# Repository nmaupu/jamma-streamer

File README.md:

# jamma-streamer

Jamma PCB video recorder and more (hardware)

# Eagle library and parts used

* `nma-eagle` library: https://github.com/nmaupu/electronics/blob/master/eagle-libs/nma-eagle.lbr
* SparkFun libraries (https://github.com/sparkfun/SparkFun-Eagle-Libraries):
  - SparkFun-Connectors
  - SparkFun-IC-Comms
  - SparkFun-PowerSymbols
  - SparkFun-Retired
* Default eagle libraries:
  - linear
  - pinhead
  - jumper

# BOM (Bill Of Materials) generation

To generate the BOM, use process described in [electronics](https://github.com/nmaupu/electronics) repository !

# RTC

## Interrupts for milliseconds counting

* We will be using the chip `DS3231`. Pin `INT/SWQ` is the one.
* Datasheet https://datasheets.maximintegrated.com/en/ds/DS3231.pdf page 13 indicates how to configure the register to enable a 1KHz signal on this pin.
* The configuration of the register should be: `0b10001000`.
* Configuration is done using I2C protocol.
* `PC3` for `pin change interrupt` on the ATmega side.

Example on how to use `PCINT` is available here: https://gist.github.com/Wollw/2598827

Example on how to configure chip registers via I2C: https://github.com/FabioCuomo/FabioCuomo-DS3231/blob/master/RTClibExtended.cpp

# Buttons detection

Buttons detection are done using shift registers (8 bits parallel in / serial out such as the 75HC165).
The code used is strongly inspired from the following tutorial:
https://playground.arduino.cc/Code/ShiftRegSN74HC165N

# uSDCARD writing

Source:
https://learn.adafruit.com/adafruit-micro-sd-breakout-board-card-tutorial?view=all

Beware: Arduino pins number and macros you can use in your code are sometimes not equivalent to what you expect when using third party libraries like the one used for SD card... One example is the pin `PB2` (Arduino's pin number 10) used for `CS`. If you use the library's macro `PB2`, it sets the pin to number `2` instead of `10`... This leads to long painful debugging session...

Here is an image with all pin numbers as a reference:

# How to program the ATMEGA328PB

## Fuses

Fuses can be calculated using: https://www.engbedded.com/fusecalc/

More info here: http://www.martyncurrey.com/arduino-atmega-328p-fuse-settings/

## Using arduino bootloader (for debugging and fast upload via IDE)

We are going to use [Minicore](https://github.com/MCUdude/MiniCore) as it supports ATmega328PB used on this project.

---

Use the following procedure:

- First install minicore boards following the [procedure](https://github.com/MCUdude/MiniCore#boards-manager-installation).

Use *arduino as ISP* method to upload the bootloader:
  - configure your IDE to use the source Arduino which will act as a programmer (ISP programmer)
  - upload Arduino ISP sketch to the arduino board to make it act as an *ISP programmer* (available as example sketch from the Arduino IDE)
  - plug all *Jamma Streamer's ICSP* to *Arduino ICSP* except *RST* both sides
  - *RST Jamma Streamer* (from ICSP) to *pin 10* of the Arduino (this will act as the reset pin)
  - plug a 10uF capacitor between Arduino RESET (capacitor +) and GND (capacitor -)

Now configure the board as per the following:

Your arduino is ready for ISP. Now you can configure to burn the bootloader:
  - `Tools > Port`: select the arduino device
  - `Tools > Burn Bootloader`

This should work as expected. From now on, you will be able to upload sketches via *NMA Jamma Streamer* USB port directly!

Fuses consideration:
  - *Minicore* is forked from *Optiboot* (official Arduino UNO bootloader) and is `512 bytes` long.
  - We are using an external crystal oscillator (and not the internal one).
  - `EEPROM` save is enabled (this avoid erasing it at each upload reducing its lifetime).
  - `BOOTSZ1` and `BOOTSZ2` are both disabled because 512 bytes can fit into the minimal 256 words (1 word = 2 bytes).
  - `BOOTRST` is set to indicate we are using a bootloader.
  - `BODLEVEL1` (2.7V) is enabled because why not.

This give the following fuses:
  - low fuse: `0xff`
  - high fuse: `0xd6`
  - extended fuse: `0xf5` (Normally, it would be `0xfd` but after burning, there is a warning so `f5` is a good value)

## Without using arduino bootloader for runtime

We are using Jamma Streamer board ICSP header for this.
No need for a Arduino bootloader, we will be uploading sketch directly via ICSP header !

As I am using Atmega328PB (instead of P), Arduino IDE is not recognizing at first, we need to install this first to have the board available in Arduino’s IDE later on:
https://github.com/nmaupu/ATmega328PB-Testing

---

Plug cables as follow (using Arduino Duemilanove or Mega):

- All ICSP to Arduino ICSP except RST both sides
- RST Jamma Streamer (from icsp) to pin 10 of the arduino
- Plug Arduino via USB to computer and upload ArduinoISP sketch onto it.
- plug a 10uF capacitor between Arduino RESET (capacitor +) and GND (capacitor -)
- select tools > boards > atmega328PB Crystal Clock
- `sketch > Upload using programmer`

This will program the NMA Jamma Streamer ATmega328PB !

## Burn / read fuses (use the crystal oscillator instead of internal one)

Use an external Arduino board to act as an ISP programmer like before:

- All ICSP to Arduino ICSP except RST both sides
- RST Jamma Streamer (from icsp) to pin 10 of the arduino
- Plug Arduino via USB to computer and upload ArduinoISP sketch onto it.
- plug a 10uF capacitor between Arduino RESET (capacitor +) and GND (capacitor -)

To read the fuses, simply execute:
```
avrdude -C /Users/nicolas_maupu/Library/Arduino15/packages/MiniCore/hardware/avr/2.0.5/avrdude.conf \
  -p atmega328pb -c stk500v1 -P /dev/cu.usbmodem141101 -b19200 \
  -U hfuse:r:-:h -U efuse:r:-:h -U lfuse:r:-:h
```

To burn fuses:
```
avrdude -C /Users/nicolas_maupu/Library/Arduino15/packages/MiniCore/hardware/avr/2.0.5/avrdude.conf \
  -v -p atmega328pb -c stk500v1 -P /dev/cu.usbmodem141101 -b19200 \
  -e -Ulock:w:0x3f:m -Uefuse:w:0xF5:m -Uhfuse:w:0xd6:m -Ulfuse:w:0xff:m 
```

To burn the Minicore bootloader:
```
avrdude -C /Users/nicolas_maupu/Library/Arduino15/packages/MiniCore/hardware/avr/2.0.5/avrdude.conf \
  -v -p atmega328pb -c stk500v1 -P /dev/cu.usbmodem141101 -b19200 \
  -Uflash:w:$HOME/Library/Arduino15/packages/MiniCore/hardware/avr/2.0.5/bootloaders/optiboot_flash/bootloaders/atmega328pb/16000000L/optiboot_flash_atmega328pb_UART0_115200_16000000L_B5.hex:i \
  -Ulock:w:0x0f:m 
```

# Thanks

- https://github.com/Shinichi-Ohki/JAMMA_connector_for_eagle
- https://github.com/watterott/wattuino

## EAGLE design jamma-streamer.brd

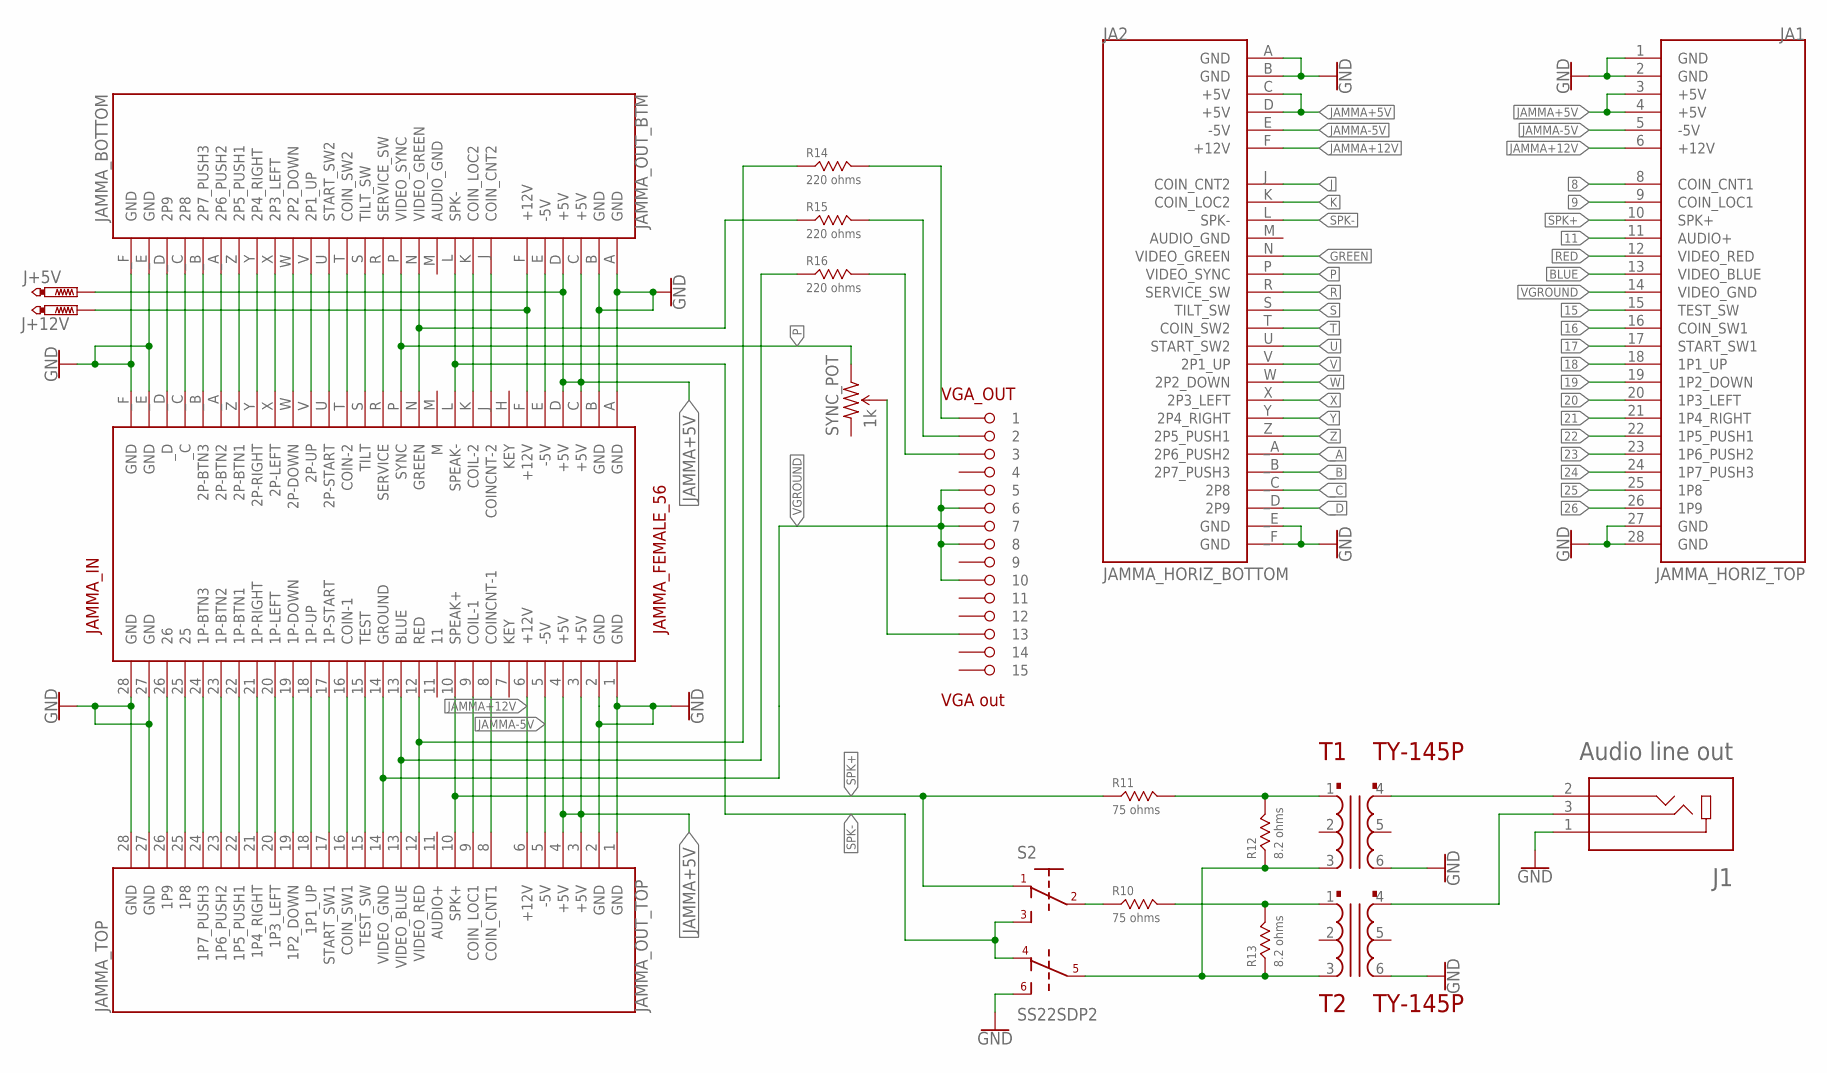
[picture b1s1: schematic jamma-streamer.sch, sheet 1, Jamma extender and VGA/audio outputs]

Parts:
J1: Audio line out; CUI_SJ1-3523N
J+5V, J+12V: PTR1TP15SQ; TP15SQ
JA1: JAMMA_HORIZ_TOP
JA2: JAMMA_HORIZ_BOTTOM
JAMMA_IN: JAMMA_FEMALE_56
JAMMA_OUT_BTM: JAMMA_BOTTOM
JAMMA_OUT_TOP: JAMMA_TOP
R10, R11: 75 ohms; TE_3550_SERIES; MOUSER_REF 279-355075RFT
R12, R13: 8.2 ohms; TE_3550_SERIES; MOUSER_REF 279-35508R2JT
R14, R15, R16: 220 ohms; RESC3225X70N
S2: SS22SDP2; SS22SDP2(DPDT)
SYNC_POT: 1k; TRIM_POT_PTH
T1, T2: TY-145P; TRIAD-TY-145P
VGA_OUT: VGA out; HARTING-DSUB-15-FEMALE

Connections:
8: JA1.8 (COIN_CNT1), JAMMA_IN.8 (COINCNT-1), JAMMA_OUT_TOP.8 (COIN_CNT1)
9: JA1.9 (COIN_LOC1), JAMMA_IN.9 (COIL-1), JAMMA_OUT_TOP.9 (COIN_LOC1)
11: JA1.11 (AUDIO+)
15: JA1.15 (TEST_SW), JAMMA_IN.15 (TEST), JAMMA_OUT_TOP.15 (TEST_SW); also elsewhere on the board
16: JA1.16 (COIN_SW1), JAMMA_IN.16 (COIN-1), JAMMA_OUT_TOP.16 (COIN_SW1); also elsewhere on the board
17: JA1.17 (START_SW1), JAMMA_IN.17 (1P-START), JAMMA_OUT_TOP.17 (START_SW1); also elsewhere on the board
18: JA1.18 (1P1_UP), JAMMA_IN.18 (1P-UP), JAMMA_OUT_TOP.18 (1P1_UP); also elsewhere on the board
19: JA1.19 (1P2_DOWN), JAMMA_IN.19 (1P-DOWN), JAMMA_OUT_TOP.19 (1P2_DOWN); also elsewhere on the board
20: JA1.20 (1P3_LEFT), JAMMA_IN.20 (1P-LEFT), JAMMA_OUT_TOP.20 (1P3_LEFT); also elsewhere on the board
21: JA1.21 (1P4_RIGHT), JAMMA_IN.21 (1P-RIGHT), JAMMA_OUT_TOP.21 (1P4_RIGHT); also elsewhere on the board
22: JA1.22 (1P5_PUSH1), JAMMA_IN.22 (1P-BTN1), JAMMA_OUT_TOP.22 (1P5_PUSH1); also elsewhere on the board
23: JA1.23 (1P6_PUSH2), JAMMA_IN.23 (1P-BTN2), JAMMA_OUT_TOP.23 (1P6_PUSH2); also elsewhere on the board
24: JA1.24 (1P7_PUSH3), JAMMA_IN.24 (1P-BTN3), JAMMA_OUT_TOP.24 (1P7_PUSH3); also elsewhere on the board
25: JA1.25 (1P8), JAMMA_IN.25, JAMMA_OUT_TOP.25 (1P8); also elsewhere on the board
26: JA1.26 (1P9), JAMMA_IN.26, JAMMA_OUT_TOP.26 (1P9); also elsewhere on the board
BLUE: JA1.13 (VIDEO_BLUE), JAMMA_IN.13 (BLUE), JAMMA_OUT_TOP.13 (VIDEO_BLUE), R16.1
GND: J1.1, JA1.1 (GND), JA1.2 (GND), JA1.27 (GND), JA1.28 (GND), JA2.A (GND), JA2.B (GND), JA2._E (GND), JA2._F (GND), JAMMA_IN.1 (GND), JAMMA_IN.2 (GND), JAMMA_IN.27 (GND), JAMMA_IN.28 (GND), JAMMA_IN.A (GND), JAMMA_IN.B (GND), JAMMA_IN._E (GND), JAMMA_IN._F (GND), JAMMA_OUT_BTM.A (GND), JAMMA_OUT_BTM.B (GND), JAMMA_OUT_BTM._E (GND), JAMMA_OUT_BTM._F (GND), JAMMA_OUT_TOP.1 (GND), JAMMA_OUT_TOP.2 (GND), JAMMA_OUT_TOP.27 (GND), JAMMA_OUT_TOP.28 (GND), S2.6, T1.6, T2.6; also elsewhere on the board
GREEN: JA2.N (VIDEO_GREEN), JAMMA_IN.N (GREEN), JAMMA_OUT_BTM.N (VIDEO_GREEN), R15.1
J: JA2.J (COIN_CNT2), JAMMA_IN.J (COINCNT-2), JAMMA_OUT_BTM.J (COIN_CNT2)
JAMMA+5V: J+5V.TP, JA1.3 (+5V), JA1.4 (+5V), JA2.C (+5V), JA2.D (+5V), JAMMA_IN.3 (+5V), JAMMA_IN.4 (+5V), JAMMA_IN.C (+5V), JAMMA_IN.D (+5V), JAMMA_OUT_BTM.C (+5V), JAMMA_OUT_BTM.D (+5V), JAMMA_OUT_TOP.3 (+5V), JAMMA_OUT_TOP.4 (+5V)
JAMMA+12V: J+12V.TP, JA1.6 (+12V), JA2.F (+12V), JAMMA_IN.6 (+12V), JAMMA_IN.F (+12V), JAMMA_OUT_BTM.F (+12V), JAMMA_OUT_TOP.6 (+12V); also elsewhere on the board
JAMMA-5V: JA1.5 (-5V), JA2.E (-5V), JAMMA_IN.5 (-5V), JAMMA_IN.E (-5V), JAMMA_OUT_BTM.E (-5V), JAMMA_OUT_TOP.5 (-5V)
K: JA2.K (COIN_LOC2), JAMMA_IN.K (COIL-2), JAMMA_OUT_BTM.K (COIN_LOC2)
unnamed: R14.2, VGA_OUT.1
unnamed: R15.2, VGA_OUT.2
unnamed: SYNC_POT.2 (WIPER), VGA_OUT.13
unnamed: R10.1, S2.2
unnamed: R11.2, R12.2, T1.1
unnamed: R10.2, R13.2, T2.1
unnamed: R16.2, VGA_OUT.3
unnamed: R12.1, R13.1, S2.5, T1.3, T2.3
unnamed: J1.2, T1.4
unnamed: J1.3, T2.4
P: JA2.P (VIDEO_SYNC), JAMMA_IN.P (SYNC), JAMMA_OUT_BTM.P (VIDEO_SYNC), SYNC_POT.1 (CCW)
R: JA2.R (SERVICE_SW), JAMMA_IN.R (SERVICE), JAMMA_OUT_BTM.R (SERVICE_SW); also elsewhere on the board
RED: JA1.12 (VIDEO_RED), JAMMA_IN.12 (RED), JAMMA_OUT_TOP.12 (VIDEO_RED), R14.1
S: JA2.S (TILT_SW), JAMMA_IN.S (TILT), JAMMA_OUT_BTM.S (TILT_SW)
SPK+: JA1.10 (SPK+), JAMMA_IN.10 (SPEAK+), JAMMA_OUT_TOP.10 (SPK+), R11.1, S2.1
SPK-: JA2.L (SPK-), JAMMA_IN.L (SPEAK-), JAMMA_OUT_BTM.L (SPK-), S2.3, S2.4
T: JA2.T (COIN_SW2), JAMMA_IN.T (COIN-2), JAMMA_OUT_BTM.T (COIN_SW2); also elsewhere on the board
U: JA2.U (START_SW2), JAMMA_IN.U (2P-START), JAMMA_OUT_BTM.U (START_SW2); also elsewhere on the board
V: JA2.V (2P1_UP), JAMMA_IN.V (2P-UP), JAMMA_OUT_BTM.V (2P1_UP); also elsewhere on the board
VGROUND: JA1.14 (VIDEO_GND), JAMMA_IN.14 (GROUND), JAMMA_OUT_TOP.14 (VIDEO_GND), VGA_OUT.5, VGA_OUT.6, VGA_OUT.7, VGA_OUT.8, VGA_OUT.10
W: JA2.W (2P2_DOWN), JAMMA_IN.W (2P-DOWN), JAMMA_OUT_BTM.W (2P2_DOWN); also elsewhere on the board
X: JA2.X (2P3_LEFT), JAMMA_IN.X (2P-LEFT), JAMMA_OUT_BTM.X (2P3_LEFT); also elsewhere on the board
Y: JA2.Y (2P4_RIGHT), JAMMA_IN.Y (2P-RIGHT), JAMMA_OUT_BTM.Y (2P4_RIGHT); also elsewhere on the board
Z: JA2.Z (2P5_PUSH1), JAMMA_IN.Z (2P-BTN1), JAMMA_OUT_BTM.Z (2P5_PUSH1); also elsewhere on the board
_A: JA2._A (2P6_PUSH2), JAMMA_IN._A (2P-BTN2), JAMMA_OUT_BTM._A (2P6_PUSH2); also elsewhere on the board
_B: JA2._B (2P7_PUSH3), JAMMA_IN._B (2P-BTN3), JAMMA_OUT_BTM._B (2P7_PUSH3); also elsewhere on the board
_C: JA2._C (2P8), JAMMA_IN._C, JAMMA_OUT_BTM._C (2P8); also elsewhere on the board
_D: JA2._D (2P9), JAMMA_IN._D, JAMMA_OUT_BTM._D (2P9); also elsewhere on the board

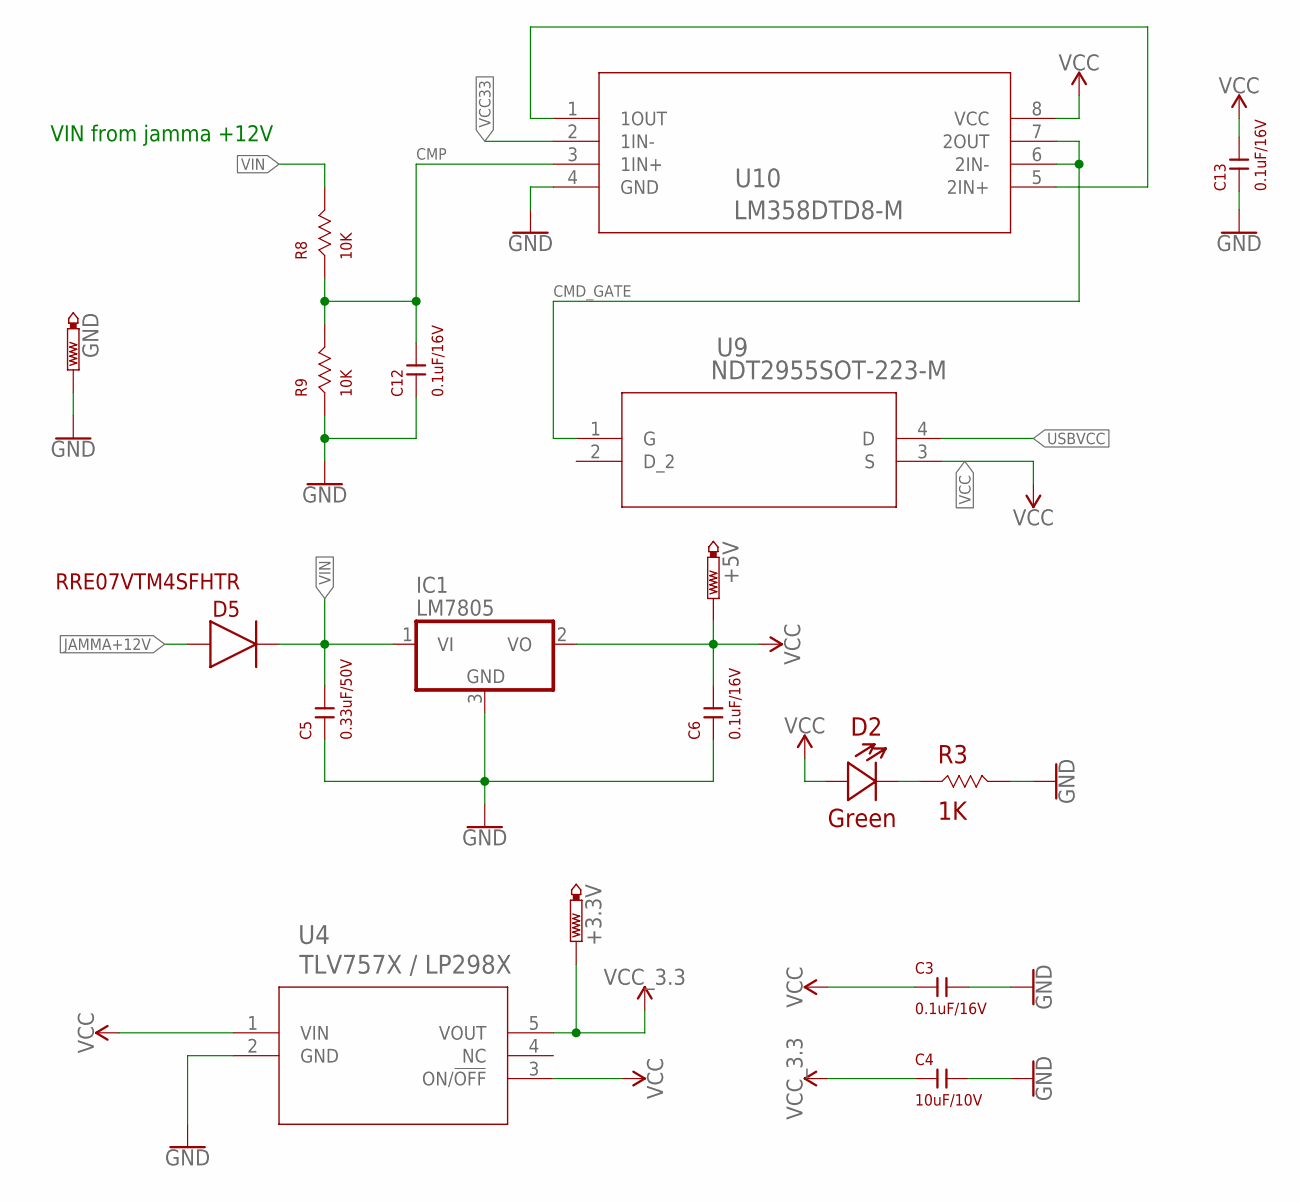
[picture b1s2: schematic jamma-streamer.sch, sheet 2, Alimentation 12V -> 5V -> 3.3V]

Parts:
+3.3V, +5V: PTR1TP15SQ; TP15SQ
C3, C6, C12, C13: 0.1uF/16V; KEMET-C1210C104K4J
C4: 10uF/10V; KEMET-C1210C106K8N
C5: 0.33uF/50V; KEMET-C1206X334K5R
D2: Green; 604-APTD1608LCGCK
D5: RRE07VTM4SFHTR; DIODE-RRE07VTM4SFHTR
GND: PTR1TP15SQ; TP15SQ
IC1: LM7805; TO252; MOUSER_REF 621-AS7805ADTR-G1
R3: 1K; 652-CHP0603FX1001ELF
R8, R9: 10K; BOURNS-CRM2512AJW-103ELF
U4: TLV757X / LP298X; DBV5-M
U9: NDT2955SOT-223-M; SOT-223-M
U10: LM358DTD8-M; D8-M

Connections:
CMD_GATE: U9.1 (G), U10.6 (2IN-), U10.7 (2OUT)
CMP: C12.1, R8.1, R9.2, U10.3 (1IN+)
GND: C3.1, C4.1, C5.2, C6.2, C12.2, C13.2, GND.TP, IC1.3 (GND), R3.2, R9.1, U4.2 (GND), U10.4 (GND); also elsewhere on the board
JAMMA+12V: D5.2; also elsewhere on the board
unnamed: D2.-, R3.1
unnamed: U10.1 (1OUT), U10.5 (2IN+)
USBVCC: U9.4 (D); also elsewhere on the board
VCC: +5V.TP, C3.2, C6.1, C13.1, D2.+, IC1.2 (VO), U4.1 (VIN), U4.3 (ON/!OFF), U9.3 (S), U10.8 (VCC); also elsewhere on the board
VCC33: U10.2 (1IN-); also elsewhere on the board
VCC_2: +3.3V.TP, C4.2, U4.5 (VOUT); also elsewhere on the board
VIN: C5.1, D5.1, IC1.1 (VI), R8.2

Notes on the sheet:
VIN from jamma +12V

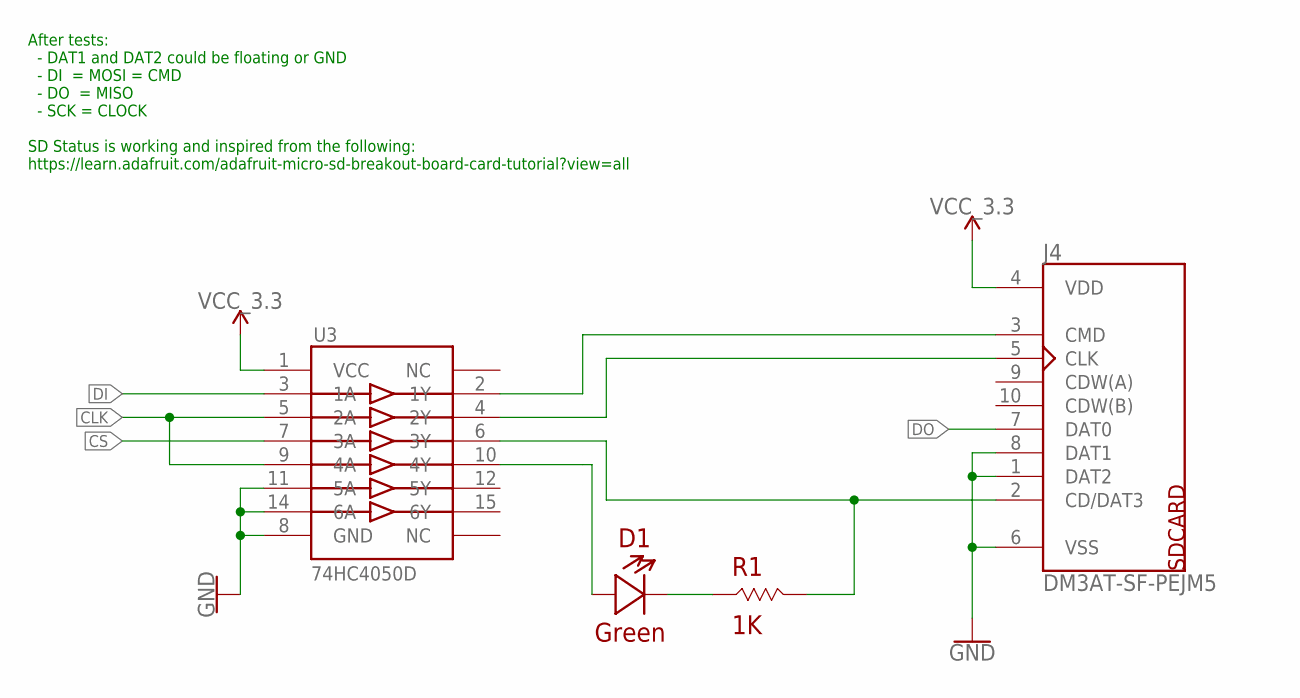
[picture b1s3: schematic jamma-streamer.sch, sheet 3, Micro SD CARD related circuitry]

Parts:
D1: Green; 604-APTD1608LCGCK
J4: DM3AT-SF-PEJM5; DM3AT-SF-PEJM5_1
R1: 1K; 652-CHP0603FX1001ELF
U3: 74HC4050D; SO16

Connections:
CLK: U3.5 (2A), U3.9 (4A); also elsewhere on the board
CS: U3.7 (3A); also elsewhere on the board
DI: U3.3 (1A); also elsewhere on the board
DO: J4.7 (DAT0); also elsewhere on the board
GND: J4.1 (DAT2), J4.6 (VSS), J4.8 (DAT1), U3.8 (GND), U3.11 (5A), U3.14 (6A); also elsewhere on the board
unnamed: D1.+, U3.10 (4Y)
unnamed: D1.-, R1.1
SD_CLK: J4.5 (CLK), U3.4 (2Y)
SD_CMD: J4.3 (CMD), U3.2 (1Y)
SD_CS: J4.2 (CD/DAT3), R1.2, U3.6 (3Y)
VCC_2: J4.4 (VDD), U3.1 (VCC); also elsewhere on the board

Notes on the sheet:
After tests: - DAT1 and DAT2 could be floating or GND - DI = MOSI = CMD - DO = MISO - SCK = CLOCK SD Status is working and inspired from the following: https://learn.adafruit.com/adafruit-micro-sd-breakout-board-card-tutorial?view=all

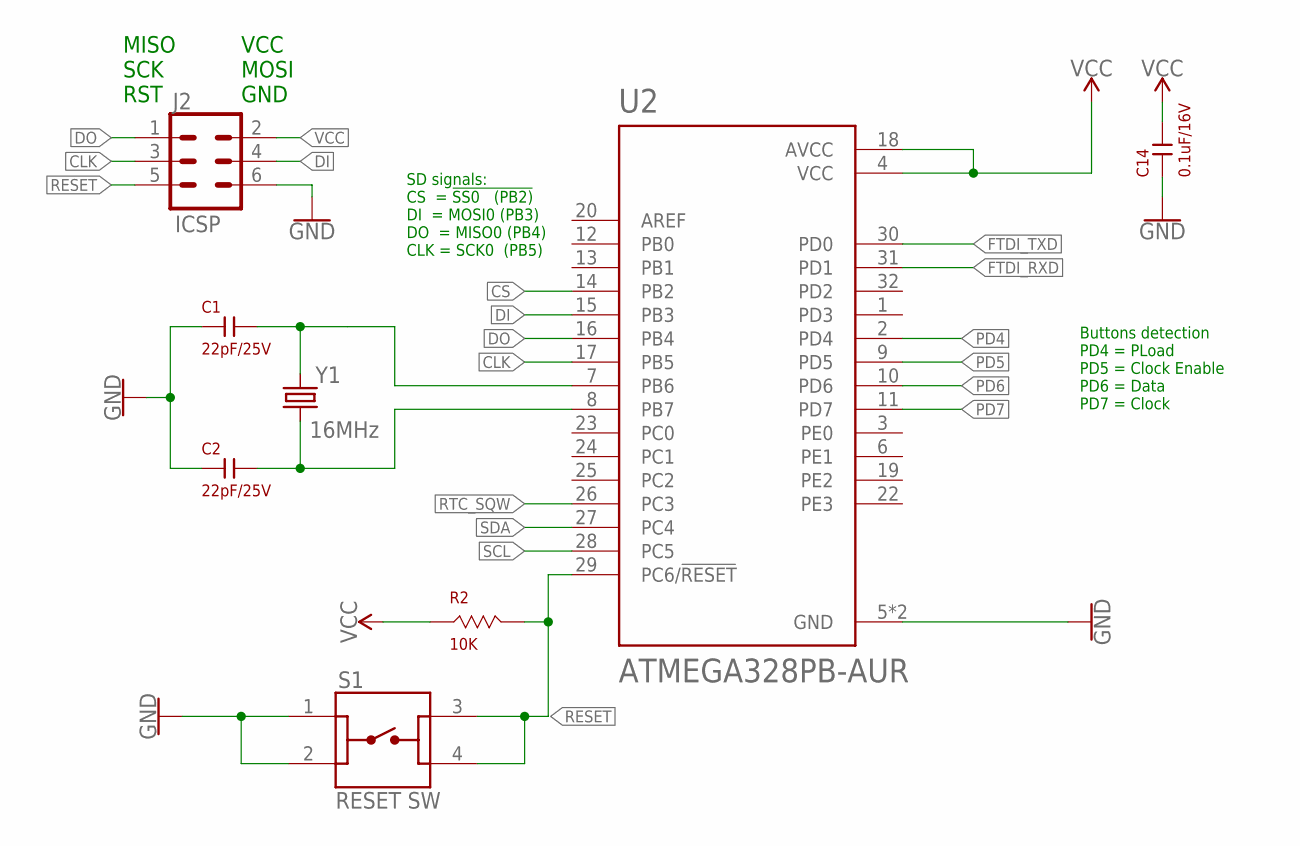
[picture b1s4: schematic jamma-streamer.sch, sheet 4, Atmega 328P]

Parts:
C1, C2: 22pF/25V; KEMET-C1206C220K3HACTU
C14: 0.1uF/16V; KEMET-C1210C104K4J
J2: ICSP; 2X3; MOUSER_REF 649-773134AE26LF
R2: 10K; BOURNS-CRM2512AJW-103ELF
S1: RESET SW; SW_1825910-7
U2: ATMEGA328PB-AUR; QFP80P900X900X120-32N
Y1: 16MHz; HC49US

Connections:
CLK: J2.3, U2.17 (PB5); also elsewhere on the board
CS: U2.14 (PB2); also elsewhere on the board
DI: J2.4, U2.15 (PB3); also elsewhere on the board
DO: J2.1, U2.16 (PB4); also elsewhere on the board
FTDI_RXD: U2.31 (PD1); also elsewhere on the board
FTDI_TXD: U2.30 (PD0); also elsewhere on the board
GND: C1.2, C2.2, C14.2, J2.6, S1.1, S1.2, U2.5 (GND), U2.21 (GND); also elsewhere on the board
PB6: C1.1, U2.7 (PB6), Y1.2
PB7: C2.1, U2.8 (PB7), Y1.1
PD4: U2.2 (PD4); also elsewhere on the board
PD5: U2.9 (PD5); also elsewhere on the board
PD6: U2.10 (PD6); also elsewhere on the board
PD7: U2.11 (PD7); also elsewhere on the board
RESET: J2.5, R2.2, S1.3, S1.4, U2.29 (PC6/!RESET); also elsewhere on the board
RTC_SQW: U2.26 (PC3); also elsewhere on the board
SCL: U2.28 (PC5); also elsewhere on the board
SDA: U2.27 (PC4); also elsewhere on the board
VCC: C14.1, J2.2, R2.1, U2.4 (VCC), U2.18 (AVCC); also elsewhere on the board

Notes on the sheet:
SD signals: CS = !SS0 (PB2) DI = MOSI0 (PB3) DO = MISO0 (PB4) CLK = SCK0 (PB5)
Buttons detection PD4 = PLoad PD5 = Clock Enable PD6 = Data PD7 = Clock
MISO SCK RST
VCC MOSI GND

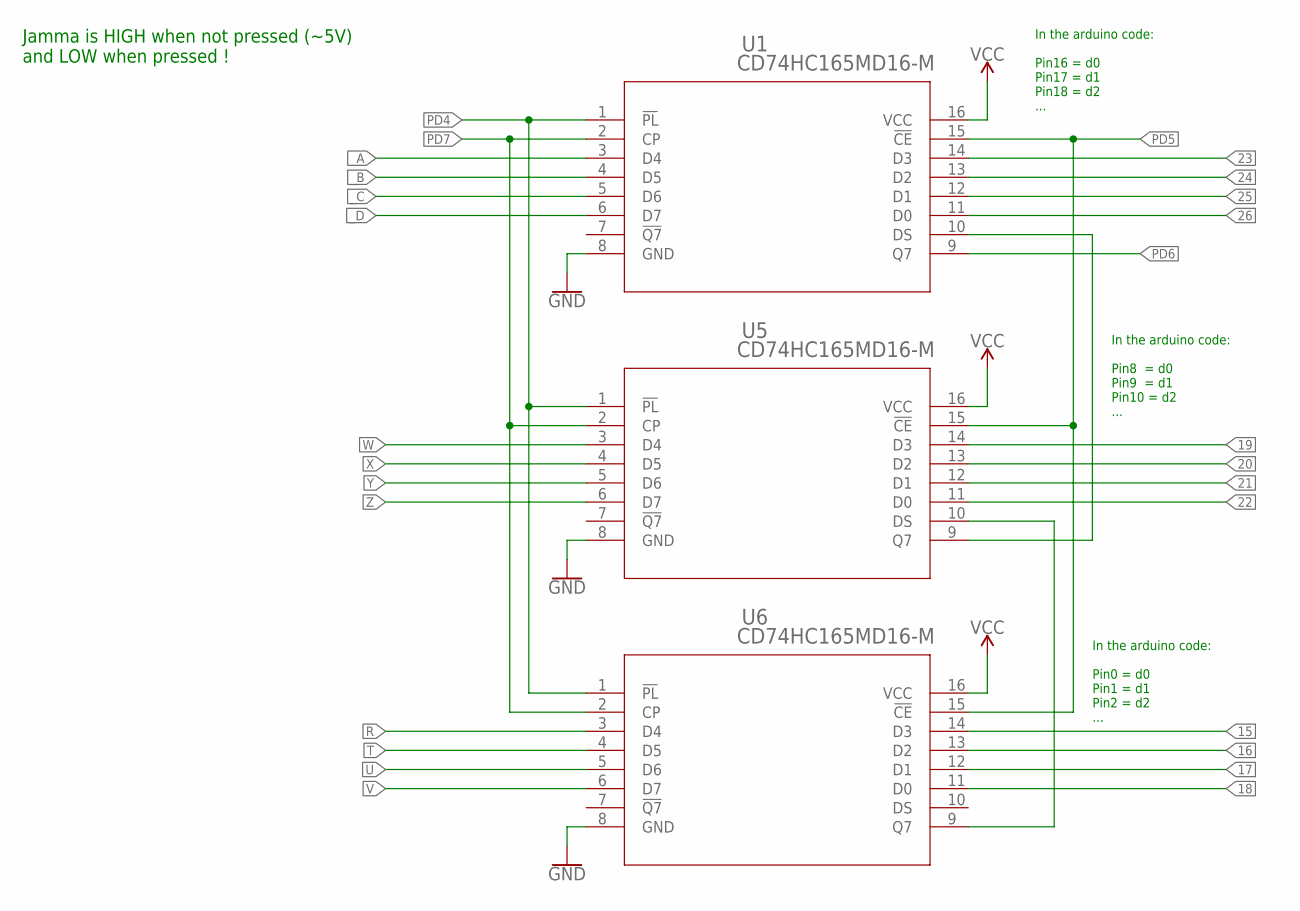
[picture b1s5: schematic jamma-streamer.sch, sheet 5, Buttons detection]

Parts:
U1, U5, U6: CD74HC165MD16-M; D16-M

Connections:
15: U6.14 (D3); also elsewhere on the board
16: U6.13 (D2); also elsewhere on the board
17: U6.12 (D1); also elsewhere on the board
18: U6.11 (D0); also elsewhere on the board
19: U5.14 (D3); also elsewhere on the board
20: U5.13 (D2); also elsewhere on the board
21: U5.12 (D1); also elsewhere on the board
22: U5.11 (D0); also elsewhere on the board
23: U1.14 (D3); also elsewhere on the board
24: U1.13 (D2); also elsewhere on the board
25: U1.12 (D1); also elsewhere on the board
26: U1.11 (D0); also elsewhere on the board
GND: U1.8 (GND), U5.8 (GND), U6.8 (GND); also elsewhere on the board
unnamed: U5.10 (DS), U6.9 (Q7)
unnamed: U1.10 (DS), U5.9 (Q7)
PD4: U1.1 (!PL), U5.1 (!PL), U6.1 (!PL); also elsewhere on the board
PD5: U1.15 (!CE), U5.15 (!CE), U6.15 (!CE); also elsewhere on the board
PD6: U1.9 (Q7); also elsewhere on the board
PD7: U1.2 (CP), U5.2 (CP), U6.2 (CP); also elsewhere on the board
R: U6.3 (D4); also elsewhere on the board
T: U6.4 (D5); also elsewhere on the board
U: U6.5 (D6); also elsewhere on the board
V: U6.6 (D7); also elsewhere on the board
VCC: U1.16 (VCC), U5.16 (VCC), U6.16 (VCC); also elsewhere on the board
W: U5.3 (D4); also elsewhere on the board
X: U5.4 (D5); also elsewhere on the board
Y: U5.5 (D6); also elsewhere on the board
Z: U5.6 (D7); also elsewhere on the board
_A: U1.3 (D4); also elsewhere on the board
_B: U1.4 (D5); also elsewhere on the board
_C: U1.5 (D6); also elsewhere on the board
_D: U1.6 (D7); also elsewhere on the board

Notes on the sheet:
Jamma is HIGH when not pressed (~5V) and LOW when pressed !
In the arduino code: Pin0 = d0 Pin1 = d1 Pin2 = d2 ...
In the arduino code: Pin8 = d0 Pin9 = d1 Pin10 = d2 ...
In the arduino code: Pin16 = d0 Pin17 = d1 Pin18 = d2 ...

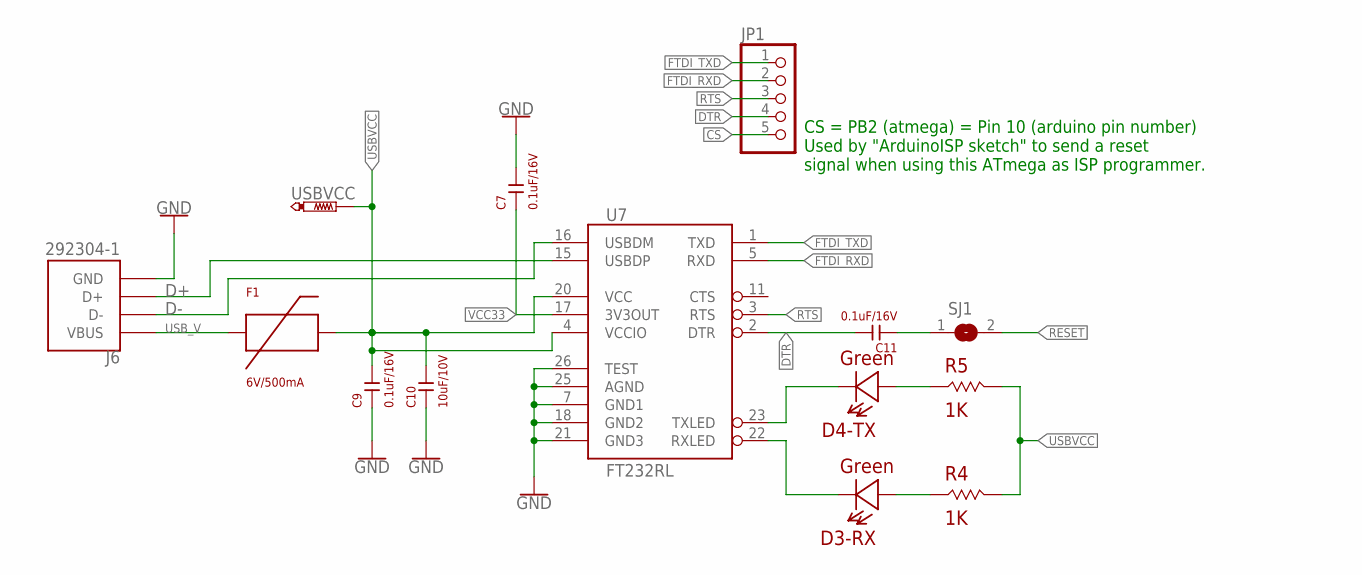
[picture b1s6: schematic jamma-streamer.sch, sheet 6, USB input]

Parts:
C7, C9, C11: 0.1uF/16V; KEMET-C1210C104K4J
C10: 10uF/10V; KEMET-C1210C106K8N
D3-RX, D4-TX: Green; 604-APTD1608LCGCK
F1: 6V/500mA; FUSE-1206L050YR
J6: 292304-1; TE_292304-1
JP1: PINHD-1X5; 1X05; MOUSER_REF 798-A23PA254DSA71
R4, R5: 1K; 652-CHP0603FX1001ELF
SJ1: SJ
U7: FT232RL; SSOP28DB
USBVCC: PTR1TP15SQ; TP15SQ

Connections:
CS: JP1.5; also elsewhere on the board
D+: J6.3 (D+), U7.15 (USBDP)
D-: J6.2 (D-), U7.16 (USBDM)
DTR: C11.1, JP1.4, U7.2 (DTR)
FTDI_RXD: JP1.2, U7.5 (RXD); also elsewhere on the board
FTDI_TXD: JP1.1, U7.1 (TXD); also elsewhere on the board
GND: C7.1, C9.2, C10.2, J6.4 (GND), U7.7 (GND1), U7.18 (GND2), U7.21 (GND3), U7.25 (AGND), U7.26 (TEST); also elsewhere on the board
unnamed: D3-RX.-, U7.22 (RXLED)
unnamed: C11.2, SJ1.1
unnamed: D4-TX.-, U7.23 (TXLED)
unnamed: D4-TX.+, R5.1
unnamed: D3-RX.+, R4.1
RESET: SJ1.2; also elsewhere on the board
RTS: JP1.3, U7.3 (RTS)
USBVCC: C9.1, C10.1, F1.2, R4.2, R5.2, U7.4 (VCCIO), U7.20 (VCC), USBVCC.TP; also elsewhere on the board
USB_V: F1.1, J6.1 (VBUS)
VCC33: C7.2, U7.17 (3V3OUT); also elsewhere on the board

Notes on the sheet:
CS = PB2 (atmega) = Pin 10 (arduino pin number) Used by "ArduinoISP sketch" to send a reset signal when using this ATmega as ISP programmer.

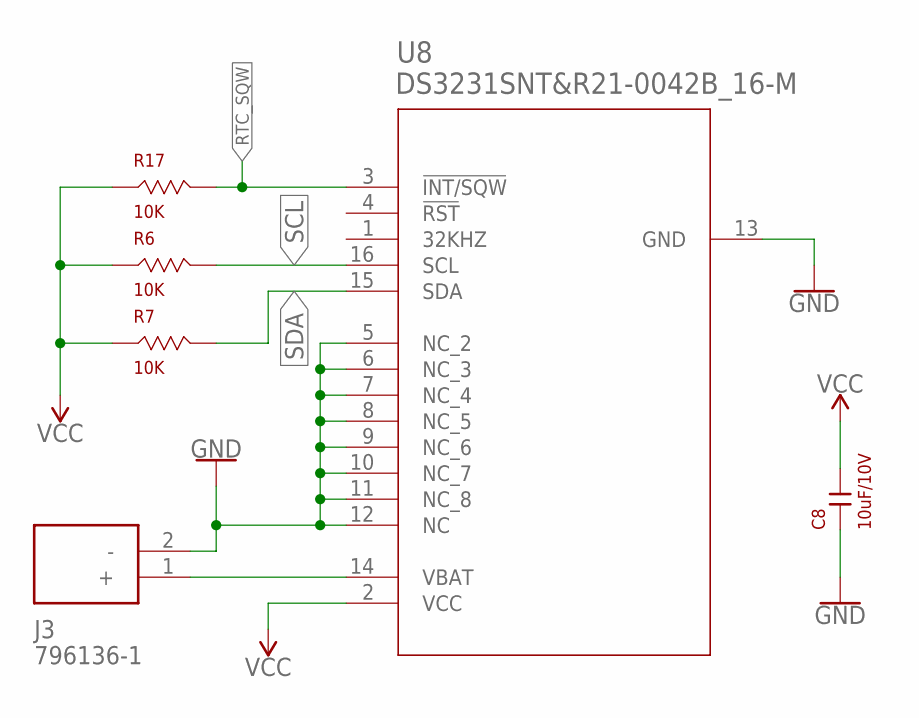
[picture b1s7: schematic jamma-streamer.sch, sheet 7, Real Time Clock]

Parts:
C8: 10uF/10V; KEMET-C1210C106K8N
J3: 796136-1
R6, R7, R17: 10K; BOURNS-CRM2512AJW-103ELF
U8: DS3231SNT&R21-0042B_16-M; 21-0042B_16-M

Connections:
GND: C8.2, J3.2 (-), U8.5 (NC_2), U8.6 (NC_3), U8.7 (NC_4), U8.8 (NC_5), U8.9 (NC_6), U8.10 (NC_7), U8.11 (NC_8), U8.12 (NC), U8.13 (GND); also elsewhere on the board
unnamed: J3.1 (+), U8.14 (VBAT)
RTC_SQW: R17.2, U8.3 (!INT/SQW); also elsewhere on the board
SCL: R6.2, U8.16 (SCL); also elsewhere on the board
SDA: R7.2, U8.15 (SDA); also elsewhere on the board
VCC: C8.1, R6.1, R7.1, R17.1, U8.2 (VCC); also elsewhere on the board

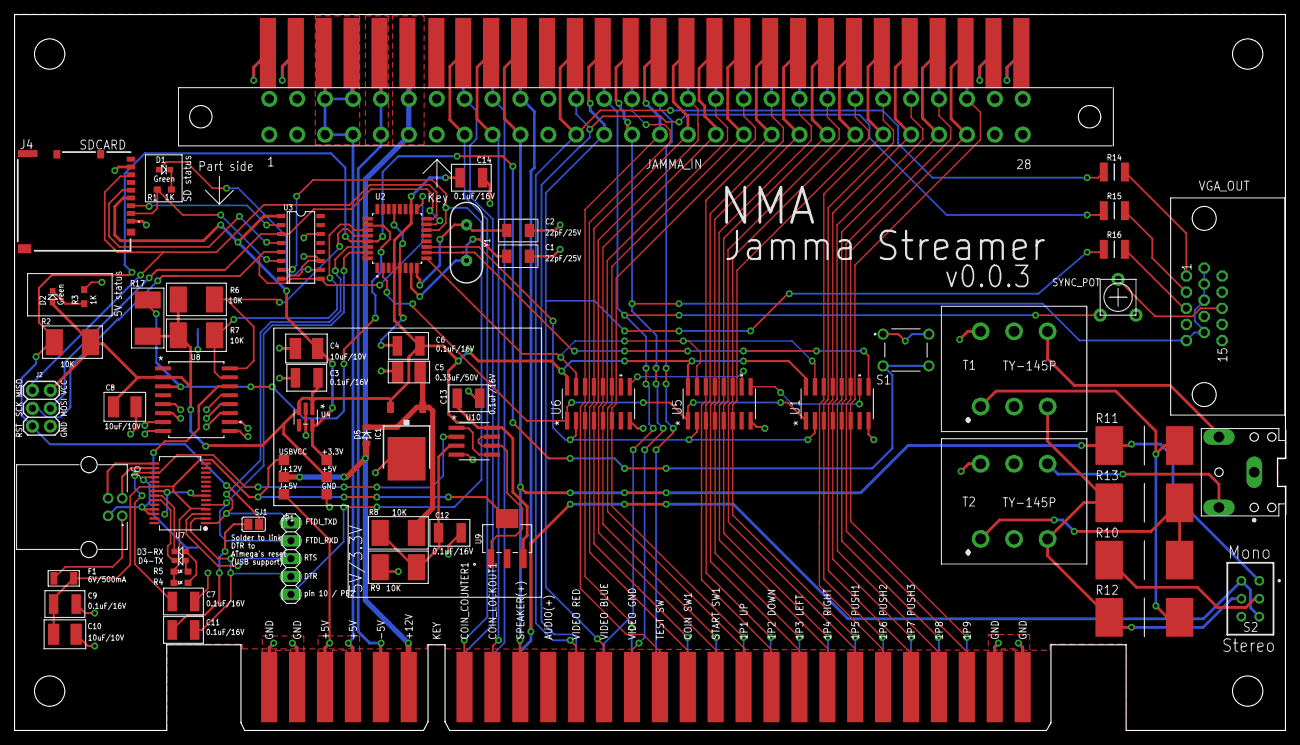
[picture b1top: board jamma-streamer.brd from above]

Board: 2 copper layers, 180.3 x 101.6 mm, 73 parts (1 on the bottom side), 93 nets.

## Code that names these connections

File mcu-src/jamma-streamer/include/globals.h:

#ifndef __GLOBALS_HEADER__
#define __GLOBALS_HEADER__

#include <Arduino.h>

#define APP_NAME "NMA Jamma Streamer"
#ifndef APP_VERSION
#define APP_VERSION "master"
#endif

// Special attention to pin numbers because Arduino library pinout macros can be
// confusing...
// As far as I know, PDx are ok whereas PBx are not really what I thought...

// Shift registers
#define PLOAD PD4   // PD4 = Arduino pin 4
#define ENABLE PD5  // PD5 = Arduino pin 5
#define DATA PD6    // PD6 = Arduino pin 6
#define CLOCK PD7   // PD7 = Arduino pin 7

// SD card
#define SD_CS 10    // PB2 = Arduino pin 10 (SS)
#define SD_MOSI 11  // PB3 = Arduino pin 11 (MOSI)
#define SD_MISO 12  // PB4 = Arduino pin 12 (MISO)
#define SD_CLK 13   // PB5 = Arduino pin 13 (SCK)

// Delay in main loop if need be
#ifndef REFRESH_DELAY_US
#define REFRESH_DELAY_US 100000
#endif

// Serial communication speed
#ifndef SERIAL_SPEED
#define SERIAL SPEED 19600
#endif

// Control register to generate a square wave (1KHz) on RTC's SQW pin to count milliseconds via interrupt.
// See page 13 - https://www.mouser.com/datasheet/2/256/DS3231-1513891.pdf
// RS2 RS1 = 1 0 for ~1kHz square wave
#define RTC_CONTROL_REG 0b10001000

// RTC / ATmega interrupt pins configuration
#define SWQ_PIN PCINT11
#define INT_PIN_GRP PINC

#endif  // __GLOBALS_HEADER__

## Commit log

2018-12-11 In progress prototype design
2018-12-11 Added Micro SDCARD circuitry
2018-12-11 Added Atmega 328p library
2018-12-12 Added atmega328p and begining wiring
2018-12-15 Schematic with atmega328p wired
2018-12-16 Adding button detection shift registers
2018-12-17 Added FTDI USB to serial RS232
2018-12-18 Alternative routing and thiner vias and routes
2018-12-20 final board v0.0.1
2018-12-21 Added more files to gitignore
2018-12-24 Better routes (unfinished) and audio circuit
2018-12-26 Rerouting + audio
2018-12-26 Updating libraries
2018-12-29 Matching outline with 3.5" jack milling layer
2019-01-13 Added information on how to program atmega chip
2019-01-27 New version including RTC and better alim
2020-06-17 Updating readme with more info
2020-06-17 New README, new schematic after burn fixing
2020-06-18 Refacto
2020-06-18 Added buttons detection atmega code
2020-06-18 Refacto to improve RAM/FLASH consumption
2020-06-19 Added Arduino pinout diagram
2020-06-19 Better routing, elec fixes, doc and sdcard ok
2020-06-19 SDCard init is now in a dedicated class
2020-06-19 Added a callback func for detecting buttons change
2020-06-20 Refacto some parts on the PCB
    - new SDCARD slot (push-push): https://www.mouser.fr/ProductDetail/798-DM3AT-SF-PEJM5
    - new microUSB connector (type B): https://www.mouser.fr/ProductDetail/806-KMMXBSMT35SB30TR
    - resistors replacement for audio (3W) -> need to replace with other
    values
    - resistors replacement for RGB (SMT)
2020-06-20 Better resistors for video and audio
2020-06-20 Reorg eagle libraries
2020-06-20 Changing battery holder to use CR2032
2020-06-21 Added RTC with milliseconds accuracy
2020-06-23 Finalization + add jamma connector horiz
2020-06-23 DRC Sparkfun ok
2020-06-23 Version sent to PCBWAY
2020-06-28 Minor changes in schematics (refab not needed)
2020-06-28 Added info to README for BOM
2020-06-28 README
2020-10-10 Setting correct pins for RTC interrupts and ms counting
2020-10-11 First try at writing events
2020-10-13 Added generated bom
2020-10-13 Simple SD card event writer

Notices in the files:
parts and their libraries:
SparkFun-Connectors: Licensing: Creative Commons ShareAlike 4.0 International - https://creativecommons.org/licenses/by-sa/4.0
